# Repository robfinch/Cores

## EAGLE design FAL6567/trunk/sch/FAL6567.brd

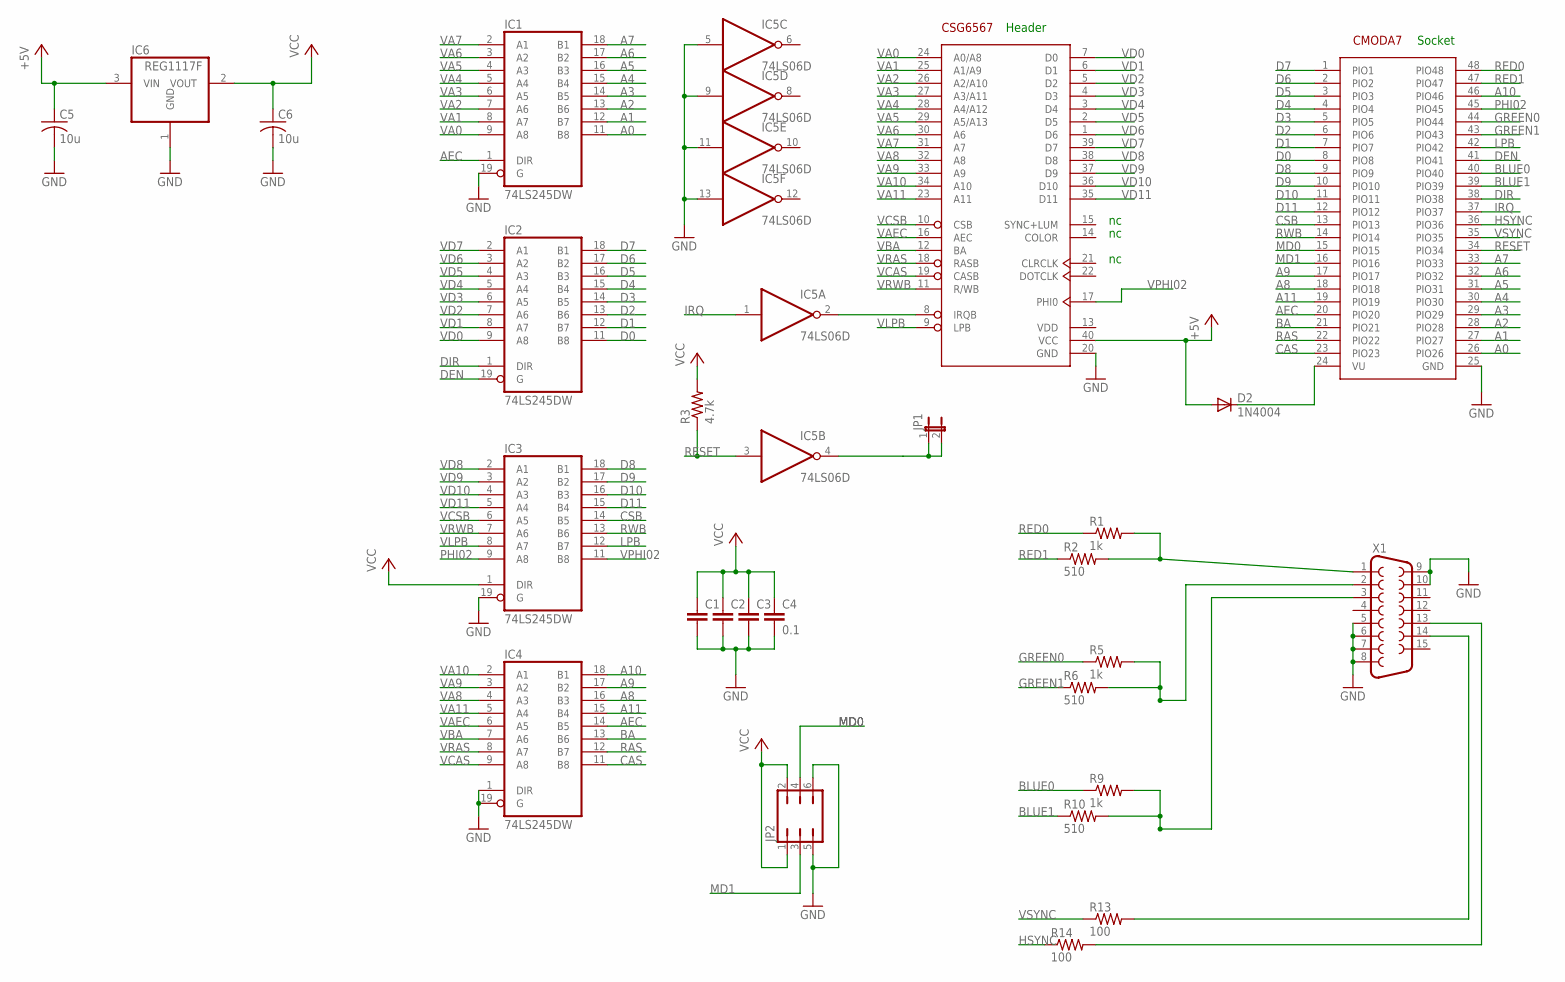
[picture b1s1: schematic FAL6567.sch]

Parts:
C1, C2, C3: C-EU050-024X044; C050-024X044
C4: 0.1; C050-024X044
C5, C6: 10u; C1206
D2: 1N4004; DO41-10
IC1, IC2, IC3, IC4: 74LS245DW; SO20W
IC5: 74LS06D; SO14
IC6: REG1117F; DD-3
JP1: JP1E; JP1
JP2: JP3Q
R1, R5, R9: 1k; 0204/7
R2, R6, R10: 510; 0204/7
R3: 4.7k; 0204/7
R13, R14: 100; 0204/7
U$1: CSG6567; DIP-40
U$2: CMODA7; DIL48
X1: F15HDV; HDF15V

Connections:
+5V: C5.1, D2.A, IC6.3 (VIN), U$1.40 (VCC)
A0: IC1.11 (B8), U$2.26 (PIO26)
A1: IC1.12 (B7), U$2.27 (PIO27)
A2: IC1.13 (B6), U$2.28 (PIO28)
A3: IC1.14 (B5), U$2.29 (PIO29)
A4: IC1.15 (B4), U$2.30 (PIO30)
A5: IC1.16 (B3), U$2.31 (PIO31)
A6: IC1.17 (B2), U$2.32 (PIO32)
A7: IC1.18 (B1), U$2.33 (PIO33)
A8: IC4.16 (B3), U$2.18 (PIO18)
A9: IC4.17 (B2), U$2.17 (PIO17)
A10: IC4.18 (B1), U$2.46 (PIO46)
A11: IC4.15 (B4), U$2.19 (PIO19)
AEC: IC1.1 (DIR), IC4.14 (B5), U$2.20 (PIO20)
BA: IC4.13 (B6), U$2.21 (PIO21)
BLUE0: R9.1, U$2.40 (PIO40)
BLUE1: R10.1, U$2.39 (PIO39)
CAS: IC4.11 (B8), U$2.23 (PIO23)
CSB: IC3.14 (B5), U$2.13 (PIO13)
D0: IC2.11 (B8), U$2.8 (PIO8)
D1: IC2.12 (B7), U$2.7 (PIO7)
D2: IC2.13 (B6), U$2.6 (PIO6)
D3: IC2.14 (B5), U$2.5 (PIO5)
D4: IC2.15 (B4), U$2.4 (PIO4)
D5: IC2.16 (B3), U$2.3 (PIO3)
D6: IC2.17 (B2), U$2.2 (PIO2)
D7: IC2.18 (B1), U$2.1 (PIO1)
D8: IC3.18 (B1), U$2.9 (PIO9)
D9: IC3.17 (B2), U$2.10 (PIO10)
D10: IC3.16 (B3), U$2.11 (PIO11)
D11: IC3.15 (B4), U$2.12 (PIO12)
DEN: IC2.19 (G), U$2.41 (PIO41)
DIR: IC2.1 (DIR), U$2.38 (PIO38)
GND: C1.2, C2.2, C3.2, C4.2, C5.2, C6.2, IC1.10 (GND), IC1.19 (G), IC2.10 (GND), IC3.10 (GND), IC3.19 (G), IC4.1 (DIR), IC4.10 (GND), IC4.19 (G), IC5.5 (I), IC5.7 (GND), IC5.9 (I), IC5.11 (I), IC5.13 (I), IC6.1 (GND), JP2.5, JP2.6, U$1.20 (GND), U$2.25 (GND), X1.5, X1.6, X1.7, X1.8, X1.9, X1.10
GREEN0: R5.1, U$2.44 (PIO44)
GREEN1: R6.1, U$2.43 (PIO43)
HSYNC: R14.1, U$2.36 (PIO36)
IRQ: IC5.1 (I), U$2.37 (PIO37)
LPB: IC3.12 (B7), U$2.42 (PIO42)
MD0: JP2.4, U$2.15 (PIO15)
MD1: JP2.3, U$2.16 (PIO16)
unnamed: IC5.2 (O), U$1.8 (IRQB)
unnamed: D2.C, U$2.24 (VU)
unnamed: R1.2, R2.2, X1.1
unnamed: IC5.4 (O), JP1.1, JP1.2
unnamed: R9.2, R10.2, X1.3
unnamed: R14.2, X1.13
unnamed: R13.2, X1.14
unnamed: R5.2, R6.2, X1.2
PHI02: IC3.9 (A8), U$2.45 (PIO45)
RAS: IC4.12 (B7), U$2.22 (PIO22)
RED0: R1.1, U$2.48 (PIO48)
RED1: R2.1, U$2.47 (PIO47)
RESET: IC5.3 (I), R3.1, U$2.34 (PIO34)
RWB: IC3.13 (B6), U$2.14 (PIO14)
VA0: IC1.9 (A8), U$1.24 (A0/A8)
VA1: IC1.8 (A7), U$1.25 (A1/A9)
VA2: IC1.7 (A6), U$1.26 (A2/A10)
VA3: IC1.6 (A5), U$1.27 (A3/A11)
VA4: IC1.5 (A4), U$1.28 (A4/A12)
VA5: IC1.4 (A3), U$1.29 (A5/A13)
VA6: IC1.3 (A2), U$1.30 (A6)
VA7: IC1.2 (A1), U$1.31 (A7)
VA8: IC4.4 (A3), U$1.32 (A8)
VA9: IC4.3 (A2), U$1.33 (A9)
VA10: IC4.2 (A1), U$1.34 (A10)
VA11: IC4.5 (A4), U$1.23 (A11)
VAEC: IC4.6 (A5), U$1.16 (AEC)
VBA: IC4.7 (A6), U$1.12 (BA)
VCAS: IC4.9 (A8), U$1.19 (CASB)
VCC: C1.1, C2.1, C3.1, C4.1, C6.1, IC1.20 (VCC), IC2.20 (VCC), IC3.1 (DIR), IC3.20 (VCC), IC4.20 (VCC), IC5.14 (VCC), IC6.2 (VOUT), JP2.1, JP2.2, R3.2
VCSB: IC3.6 (A5), U$1.10 (CSB)
VD0: IC2.9 (A8), U$1.7 (D0)
VD1: IC2.8 (A7), U$1.6 (D1)
VD2: IC2.7 (A6), U$1.5 (D2)
VD3: IC2.6 (A5), U$1.4 (D3)
VD4: IC2.5 (A4), U$1.3 (D4)
VD5: IC2.4 (A3), U$1.2 (D5)
VD6: IC2.3 (A2), U$1.1 (D6)
VD7: IC2.2 (A1), U$1.39 (D7)
VD8: IC3.2 (A1), U$1.38 (D8)
VD9: IC3.3 (A2), U$1.37 (D9)
VD10: IC3.4 (A3), U$1.36 (D10)
VD11: IC3.5 (A4), U$1.35 (D11)
VDD: U$1.13 (VDD)
VLPB: IC3.8 (A7), U$1.9 (LPB)
VPHI02: IC3.11 (B8), U$1.17 (PHI0)
VRAS: IC4.8 (A7), U$1.18 (RASB)
VRWB: IC3.7 (A6), U$1.11 (R/WB)
VSYNC: R13.1, U$2.35 (PIO35)

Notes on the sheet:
Header
Socket

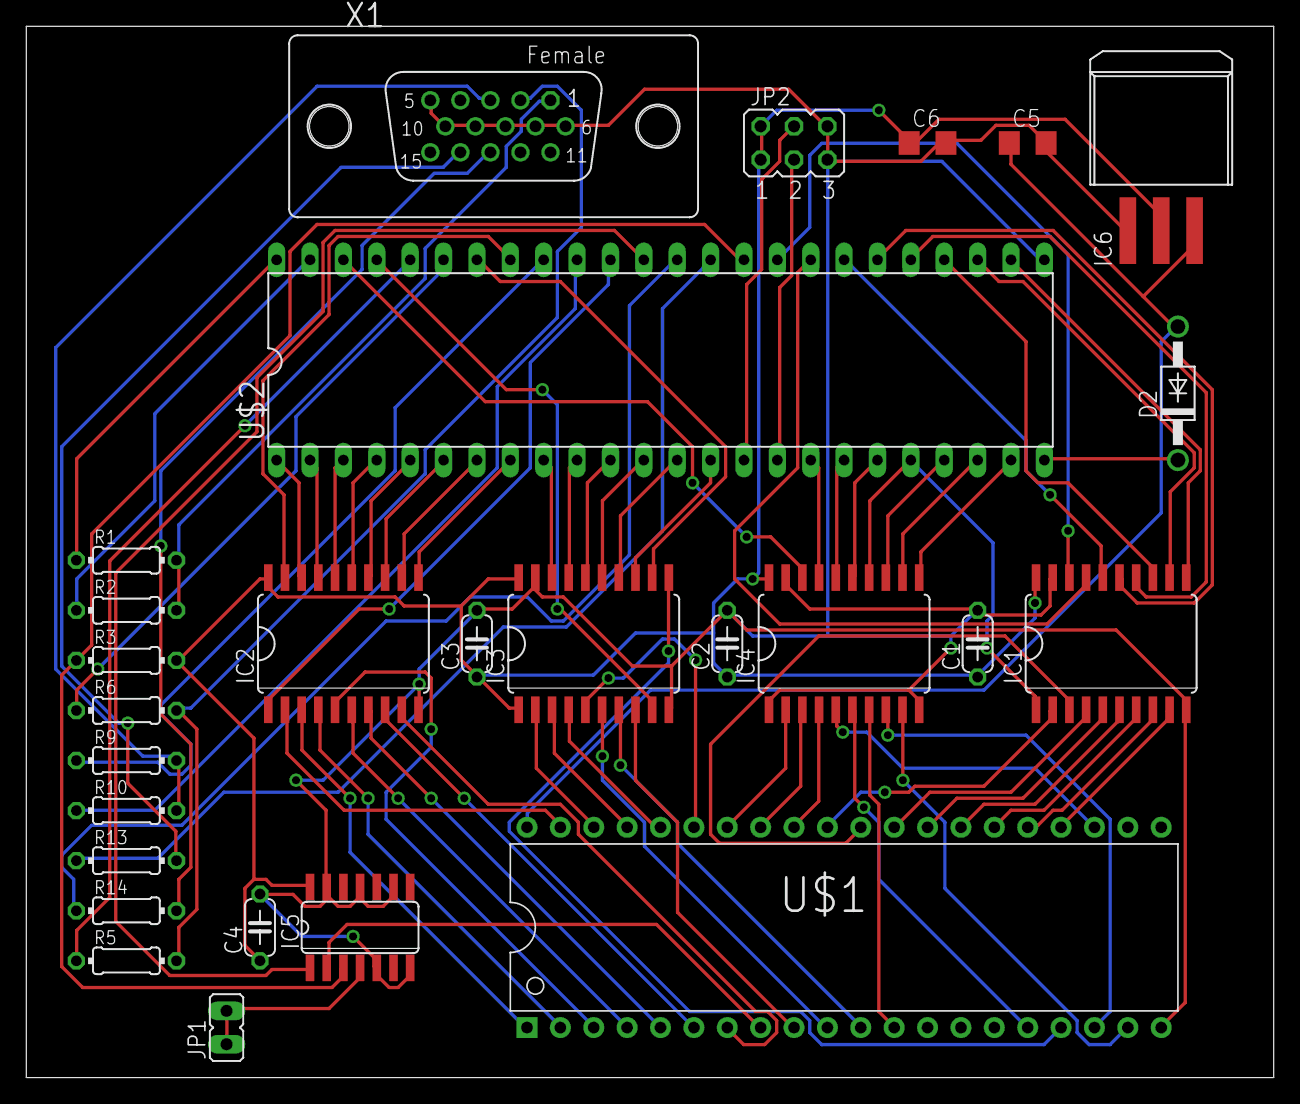
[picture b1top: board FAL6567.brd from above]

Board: 2 copper layers, 94.9 x 80.0 mm, 27 parts (0 on the bottom side), 89 nets.

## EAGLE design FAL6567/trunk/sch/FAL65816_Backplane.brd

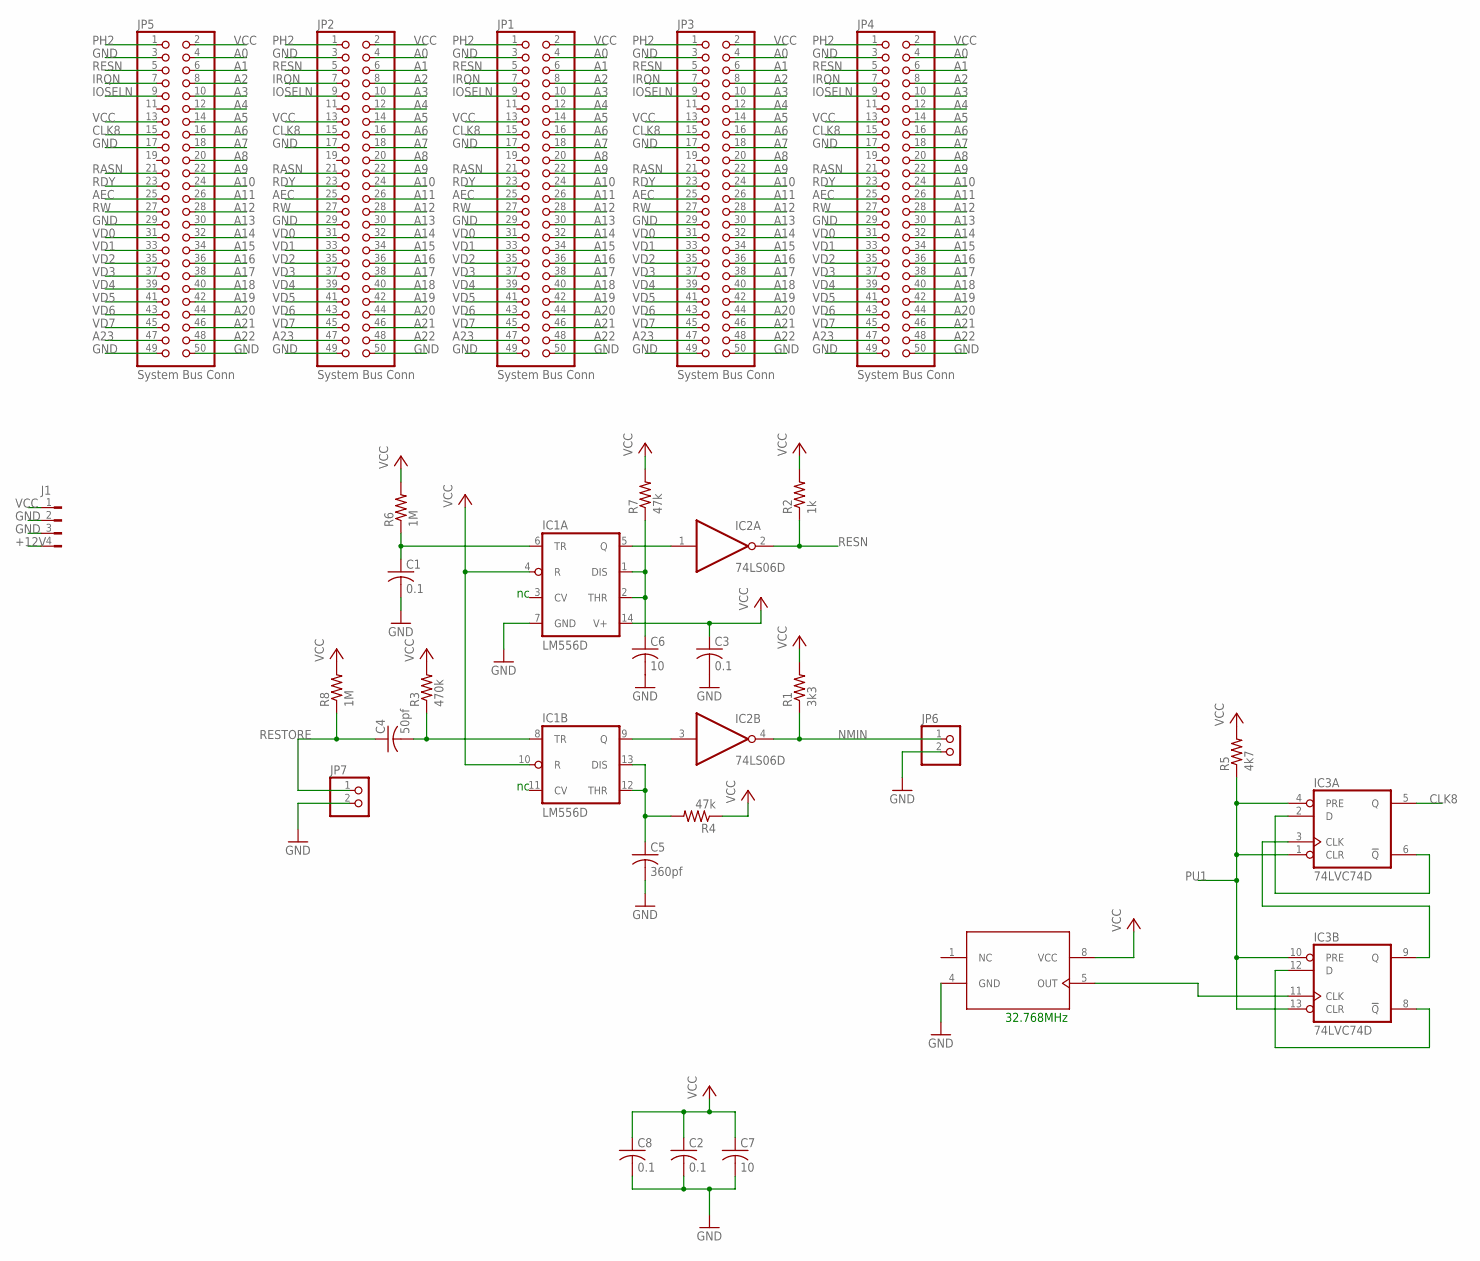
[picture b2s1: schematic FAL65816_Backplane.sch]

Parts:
C1, C2, C3, C8: 0.1; C050-024X044
C4: 50pf; C050-024X044
C5: 360pf; C050-024X044
C6, C7: 10; C050-024X044
IC1: LM556D; SO14
IC2: 74LS06D; SO14
IC3: 74LVC74D; SO14
J1: FLOPPY-4
JP1, JP2, JP3, JP4, JP5: System Bus Conn; 2X25
JP6, JP7: PINHD-1X2; 1X02
R1: 3k3; 0204/7
R2: 1k; 0204/7
R3: 470k; 0204/7
R4, R7: 47k; 0204/7
R5: 4k7; 0204/7
R6, R8: 1M; 0204/7
U$1: OSC; DIL08

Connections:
+12V: J1.4
A0: JP1.4, JP2.4, JP3.4, JP4.4, JP5.4
A1: JP1.6, JP2.6, JP3.6, JP4.6, JP5.6
A2: JP1.8, JP2.8, JP3.8, JP4.8, JP5.8
A3: JP1.10, JP2.10, JP3.10, JP4.10, JP5.10
A4: JP1.12, JP2.12, JP3.12, JP4.12, JP5.12
A5: JP1.14, JP2.14, JP3.14, JP4.14, JP5.14
A6: JP1.16, JP2.16, JP3.16, JP4.16, JP5.16
A7: JP1.18, JP2.18, JP3.18, JP4.18, JP5.18
A8: JP1.20, JP2.20, JP3.20, JP4.20, JP5.20
A9: JP1.22, JP2.22, JP3.22, JP4.22, JP5.22
A10: JP1.24, JP2.24, JP3.24, JP4.24, JP5.24
A11: JP1.26, JP2.26, JP3.26, JP4.26, JP5.26
A12: JP1.28, JP2.28, JP3.28, JP4.28, JP5.28
A13: JP1.30, JP2.30, JP3.30, JP4.30, JP5.30
A14: JP1.32, JP2.32, JP3.32, JP4.32, JP5.32
A15: JP1.34, JP2.34, JP3.34, JP4.34, JP5.34
A16: JP1.36, JP2.36, JP3.36, JP4.36, JP5.36
A17: JP1.38, JP2.38, JP3.38, JP4.38, JP5.38
A18: JP1.40, JP2.40, JP3.40, JP4.40, JP5.40
A19: JP1.42, JP2.42, JP3.42, JP4.42, JP5.42
A20: JP1.44, JP2.44, JP3.44, JP4.44, JP5.44
A21: JP1.46, JP2.46, JP3.46, JP4.46, JP5.46
A22: JP1.48, JP2.48, JP3.48, JP4.48, JP5.48
A23: JP1.47, JP2.47, JP3.47, JP4.47, JP5.47
AEC: JP1.25, JP2.25, JP3.25, JP4.25, JP5.25
CLK8: IC3.5 (Q), JP1.15, JP2.15, JP3.15, JP4.15, JP5.15
GND: C1.2, C2.2, C3.2, C5.2, C6.2, C7.2, C8.2, IC1.7 (GND), IC2.7 (GND), IC3.7 (GND), J1.2, J1.3, JP1.3, JP1.17, JP1.29, JP1.49, JP1.50, JP2.3, JP2.17, JP2.29, JP2.49, JP2.50, JP3.3, JP3.17, JP3.29, JP3.49, JP3.50, JP4.3, JP4.17, JP4.29, JP4.49, JP4.50, JP5.3, JP5.17, JP5.29, JP5.49, JP5.50, JP6.2, JP7.2, U$1.4 (GND)
IOSELN: JP1.9, JP2.9, JP3.9, JP4.9, JP5.9
IRQN: JP1.7, JP2.7, JP3.7, JP4.7, JP5.7
unnamed: IC3.3 (CLK), IC3.9 (Q)
unnamed: IC1.5 (Q), IC2.1 (I)
unnamed: IC3.8 (!Q), IC3.12 (D)
unnamed: IC1.9 (Q), IC2.3 (I)
unnamed: C1.1, IC1.6 (TR), R6.1
unnamed: IC3.11 (CLK), U$1.5 (OUT)
unnamed: IC3.2 (D), IC3.6 (!Q)
unnamed: C6.1, IC1.1 (DIS), IC1.2 (THR), R7.1
unnamed: C4.2, IC1.8 (TR), R3.1
unnamed: C5.1, IC1.12 (THR), IC1.13 (DIS), R4.2
NMIN: IC2.4 (O), JP6.1, R1.1
PH2: JP1.1, JP2.1, JP3.1, JP4.1, JP5.1
PU1: IC3.1 (CLR), IC3.4 (PRE), IC3.10 (PRE), IC3.13 (CLR), R5.1
RASN: JP1.21, JP2.21, JP3.21, JP4.21, JP5.21
RDY: JP1.23, JP2.23, JP3.23, JP4.23, JP5.23
RESN: IC2.2 (O), JP1.5, JP2.5, JP3.5, JP4.5, JP5.5, R2.1
RESTORE: C4.1, JP7.1, R8.1
RW: JP1.27, JP2.27, JP3.27, JP4.27, JP5.27
VCC: C2.1, C3.1, C7.1, C8.1, IC1.4 (R), IC1.10 (R), IC1.14 (V+), IC2.14 (VCC), IC3.14 (VCC), J1.1, JP1.2, JP1.13, JP2.2, JP2.13, JP3.2, JP3.13, JP4.2, JP4.13, JP5.2, JP5.13, R1.2, R2.2, R3.2, R4.1, R5.2, R6.2, R7.2, R8.2, U$1.8 (VCC)
VD0: JP1.31, JP2.31, JP3.31, JP4.31, JP5.31
VD1: JP1.33, JP2.33, JP3.33, JP4.33, JP5.33
VD2: JP1.35, JP2.35, JP3.35, JP4.35, JP5.35
VD3: JP1.37, JP2.37, JP3.37, JP4.37, JP5.37
VD4: JP1.39, JP2.39, JP3.39, JP4.39, JP5.39
VD5: JP1.41, JP2.41, JP3.41, JP4.41, JP5.41
VD6: JP1.43, JP2.43, JP3.43, JP4.43, JP5.43
VD7: JP1.45, JP2.45, JP3.45, JP4.45, JP5.45

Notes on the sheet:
32.768MHz

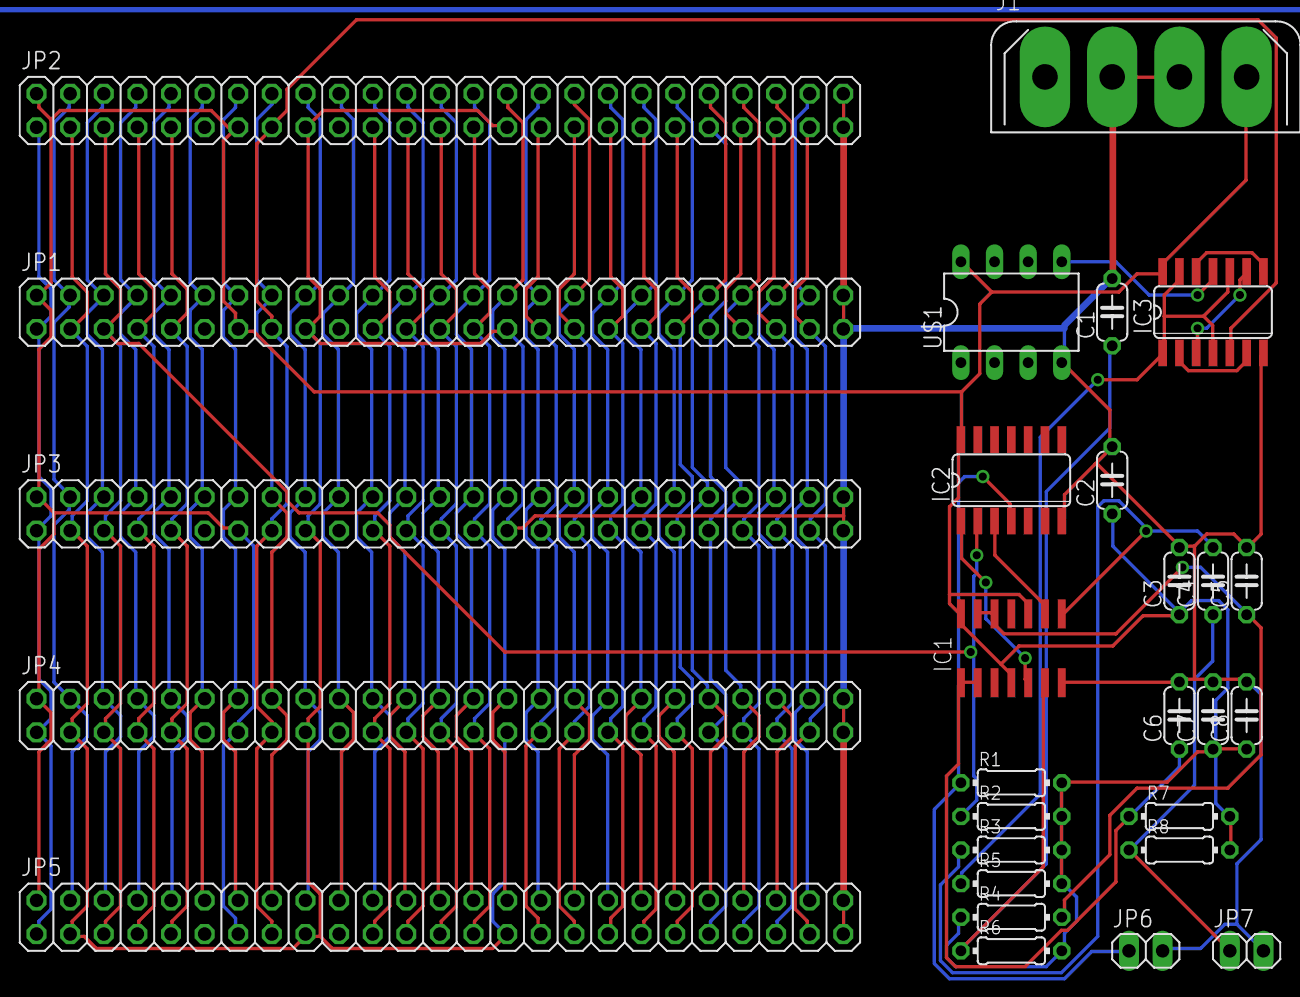
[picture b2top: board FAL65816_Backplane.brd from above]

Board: 2 copper layers, 28 parts (0 on the bottom side), 56 nets.
